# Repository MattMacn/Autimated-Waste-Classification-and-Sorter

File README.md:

# Automated Material Sorting System

## Overview

The **Automated Material Sorting System** is an embedded system designed to automatically identify and sort different types of waste.

The system uses an **ESP32 microcontroller** together with inductive, capacitive and ultrasonic sensors to identify materials and control a mechanical sorting mechanism using four servo motors.

The project combines **embedded software, electronics, PCB design and mechanical control** into a single automated system.

## Features

* Automatic material detection
* Metal detection using an inductive sensor
* Non-metal material detection using a capacitive sensor
* Ultrasonic sensing for object detection
* Automated mechanical sorting
* Four servo motors for material routing
* ESP32-based embedded control
* Custom PCB designed using KiCad
* Separate collection compartments for different materials

## System Architecture

```text

                            ^
                            |
          +-----------------+-----------------+
          |                 |                 |
          v                 v                 v
   +-------------+   +-------------+   +-------------+
   |  Inductive  |   | Capacitive  |   |  Ultrasonic |
   |   Sensor    |   |   Sensor    |   |   Sensor    |
   +-------------+   +-------------+   +-------------+
          +-----------------+-----------------+
                            |                 
                            |                                       
                            |
                            v
                  +-------------------+
                  |       ESP32       |
                  |                   |
                  |  Embedded Control |
                  +---------+---------+
                            |
                            v
                   +----------------+
                   | Material       |
                   | Classification |
                   +-------+--------+
                           |
                           v
                  +-------------------+
                  | Servo Actuators   |
                  |                   |
                  |   4 x SG90        |
                  +---------+---------+

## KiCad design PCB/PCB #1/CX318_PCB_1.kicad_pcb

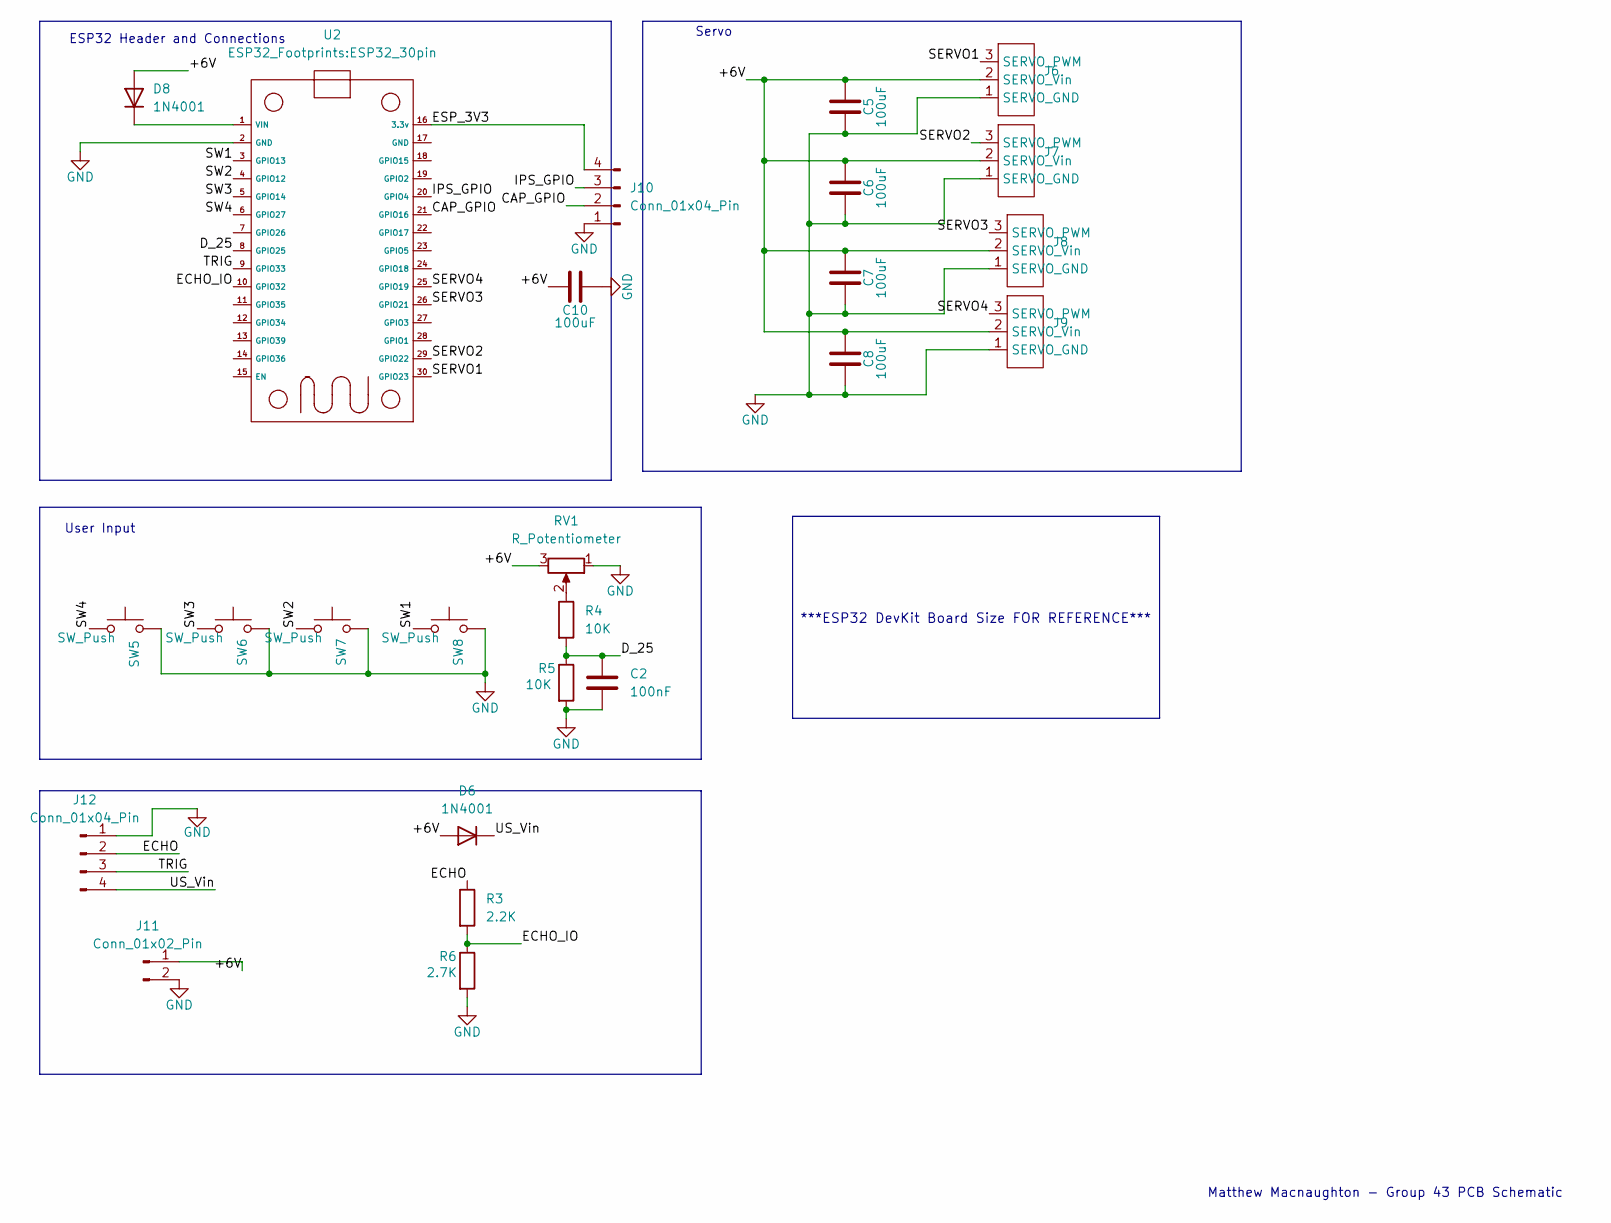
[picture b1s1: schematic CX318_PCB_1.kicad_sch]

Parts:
C2: 100nF; C_Disc_D5.0mm_W2.5mm_P5.00mm
C5, C6, C7, C8, C10: 100uF; C_Disc_D5.0mm_W2.5mm_P5.00mm
D6, D8: 1N4001; D_DO-41_SOD81_P10.16mm_Horizontal
J6, J7, J8, J9: PinHeader_1x03_P2.54mm_Vertical
J10: Conn_01x04_Pin; JST_XH_B4B-XH-A_1x04_P2.50mm_Vertical
J11: Conn_01x02_Pin; PinSocket_1x02_P2.54mm_Vertical
J12: Conn_01x04_Pin; PinSocket_1x04_P2.54mm_Vertical
R3: 2.2K; R_Axial_DIN0207_L6.3mm_D2.5mm_P7.62mm_Horizontal
R4, R5: 10K; R_Axial_DIN0207_L6.3mm_D2.5mm_P7.62mm_Horizontal
R6: 2.7K; R_Axial_DIN0207_L6.3mm_D2.5mm_P7.62mm_Horizontal
RV1: R_Potentiometer; Potentiometer_Bourns_3386P_Vertical
SW5, SW6, SW7, SW8: SW_Push; SW_PUSH_6mm
U2: ESP32_30pin

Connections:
/+6V: C5.1, C6.1, C7.1, C8.1, C10.2, D6.2 (A), D8.2 (A), J6.2 (SERVO_Vin), J7.2 (SERVO_Vin), J8.2 (SERVO_Vin), J9.2 (SERVO_Vin), J11.1, RV1.3
/CAP_GPIO: J10.2, U2.21 (GPIO16)
/D_25: C2.1, R4.2, R5.1, U2.8 (GPIO25)
/ECHO: J12.2, R3.1
/ECHO_IO: R3.2, R6.1, U2.10 (GPIO32)
/ESP_3V3: J10.4, U2.16 (3.3v)
/IPS_GPIO: J10.3, U2.20 (GPIO4)
/SERVO1: J6.3 (SERVO_PWM), U2.30 (GPIO23)
/SERVO2: J7.3 (SERVO_PWM), U2.29 (GPIO22)
/SERVO3: J8.3 (SERVO_PWM), U2.26 (GPIO21)
/SERVO4: J9.3 (SERVO_PWM), U2.25 (GPIO19)
/SW1: SW8.1, U2.3 (GPIO13)
/SW2: SW7.1, U2.4 (GPIO12)
/SW3: SW6.1, U2.5 (GPIO14)
/SW4: SW5.1, U2.6 (GPIO27)
/TRIG: J12.3, U2.9 (GPIO33)
/US_Vin: D6.1 (K), J12.4
GND: C2.2, C5.2, C6.2, C7.2, C8.2, C10.1, J6.1 (SERVO_GND), J7.1 (SERVO_GND), J8.1 (SERVO_GND), J9.1 (SERVO_GND), J10.1, J11.2, J12.1, R5.2, R6.2, RV1.1, SW5.2, SW6.2, SW7.2, SW8.2, U2.2 (GND)
unnamed: D8.1 (K), U2.1 (VIN)
unnamed: R4.1, RV1.2

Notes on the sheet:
User Input
Matthew Macnaughton - Group 43 PCB Schematic
Servo
ESP32 Header and Connections
***ESP32 DevKit Board Size FOR REFERENCE***

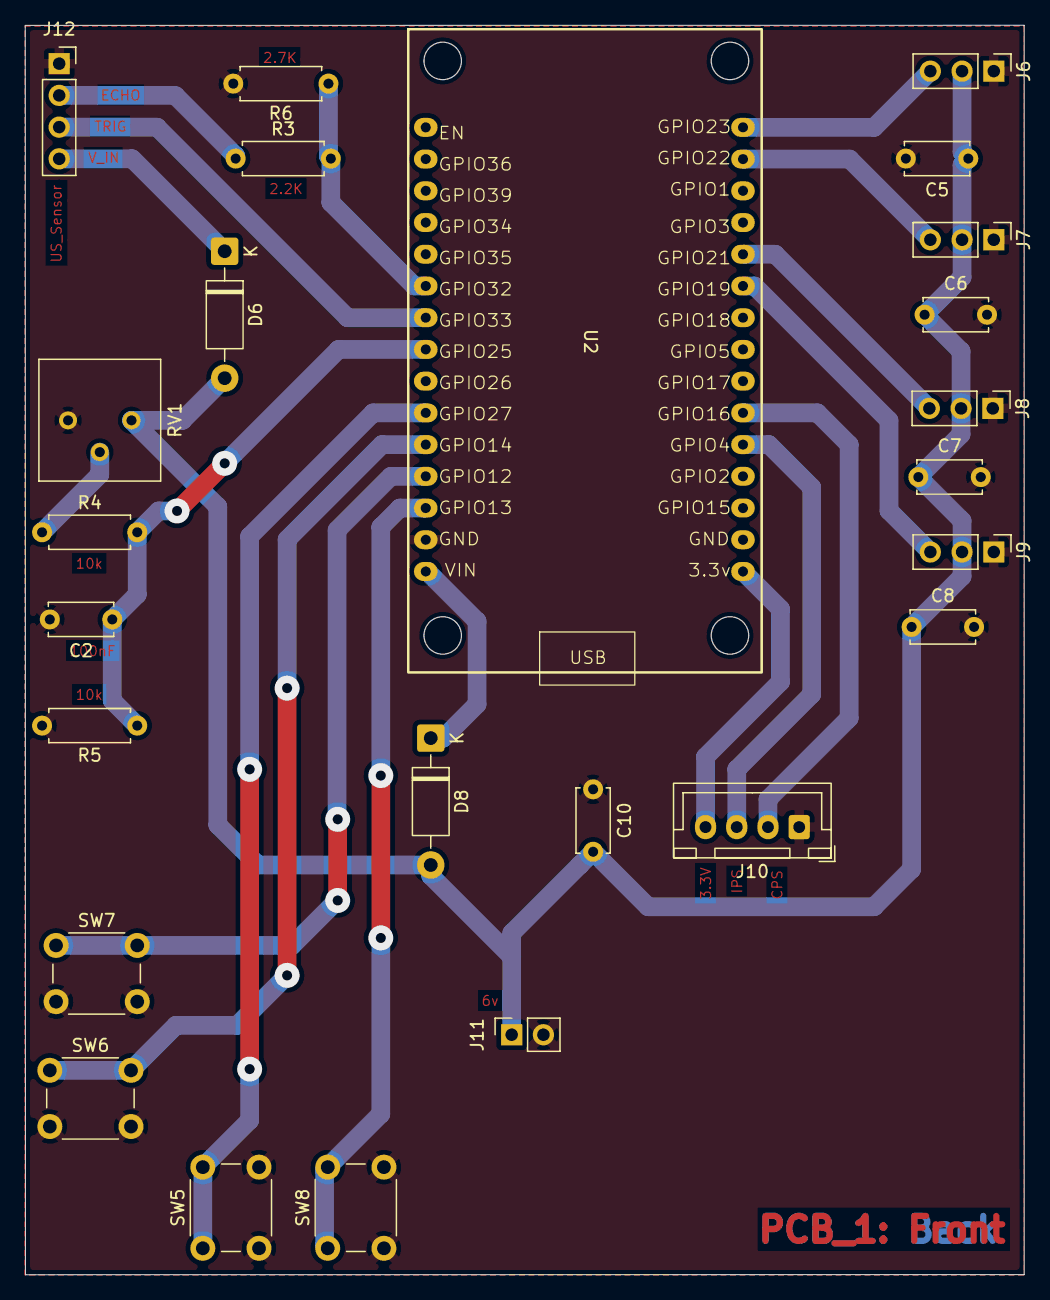
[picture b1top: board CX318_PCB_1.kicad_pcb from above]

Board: 2 copper layers, 80.0 x 100.0 mm, 25 parts (0 on the bottom side), 20 nets.

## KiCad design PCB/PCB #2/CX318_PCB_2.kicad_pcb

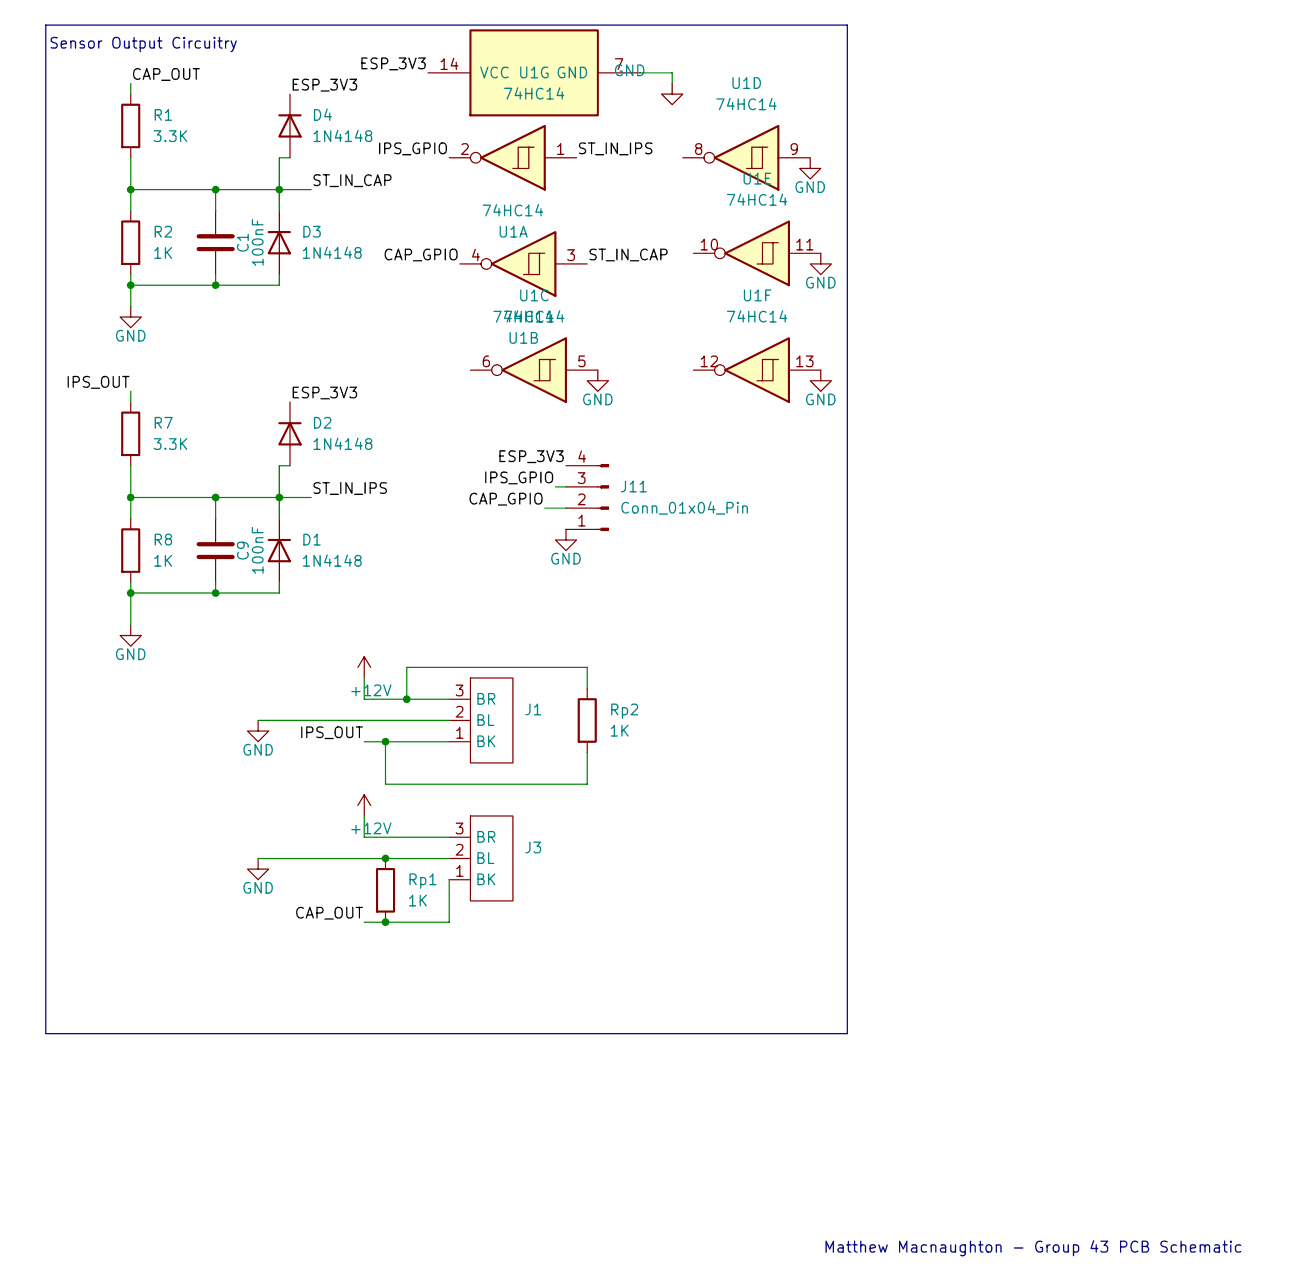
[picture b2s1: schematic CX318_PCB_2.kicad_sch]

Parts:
C1, C9: 100nF; C_Disc_D5.0mm_W2.5mm_P5.00mm
D1, D2, D3, D4: 1N4148; D_DO-35_SOD27_P7.62mm_Horizontal
J1, J3: PinHeader_1x03_P2.54mm_Vertical
J11: Conn_01x04_Pin; JST_XH_B4B-XH-A_1x04_P2.50mm_Vertical
R1, R7: 3.3K; R_Axial_DIN0207_L6.3mm_D2.5mm_P7.62mm_Horizontal
R2, R8: 1K; R_Axial_DIN0207_L6.3mm_D2.5mm_P7.62mm_Horizontal
Rp1, Rp2: 1K; R_Axial_DIN0207_L6.3mm_D2.5mm_P7.62mm_Horizontal
U1: 74HC14; DIP-14_W7.62mm

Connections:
+12V: J1.3 (BR), J3.3 (BR), Rp2.1; also elsewhere on the board
/CAP_GPIO: J11.2, U1.4
/CAP_OUT: J3.1 (BK), R1.1, Rp1.2
/ESP_3V3: D2.1 (K), D4.1 (K), J11.4, U1.14 (VCC)
/IPS_GPIO: J11.3, U1.2
/IPS_OUT: J1.1 (BK), R7.1, Rp2.2
/ST_IN_CAP: C1.1, D3.1 (K), D4.2 (A), R1.2, R2.1, U1.3
/ST_IN_IPS: C9.1, D1.1 (K), D2.2 (A), R7.2, R8.1, U1.1
GND: C1.2, C9.2, D1.2 (A), D3.2 (A), J1.2 (BL), J3.2 (BL), J11.1, R2.2, R8.2, Rp1.1, U1.5, U1.7 (GND), U1.9, U1.11, U1.13; also elsewhere on the board

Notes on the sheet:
Matthew Macnaughton - Group 43 PCB Schematic
Sensor Output Circuitry

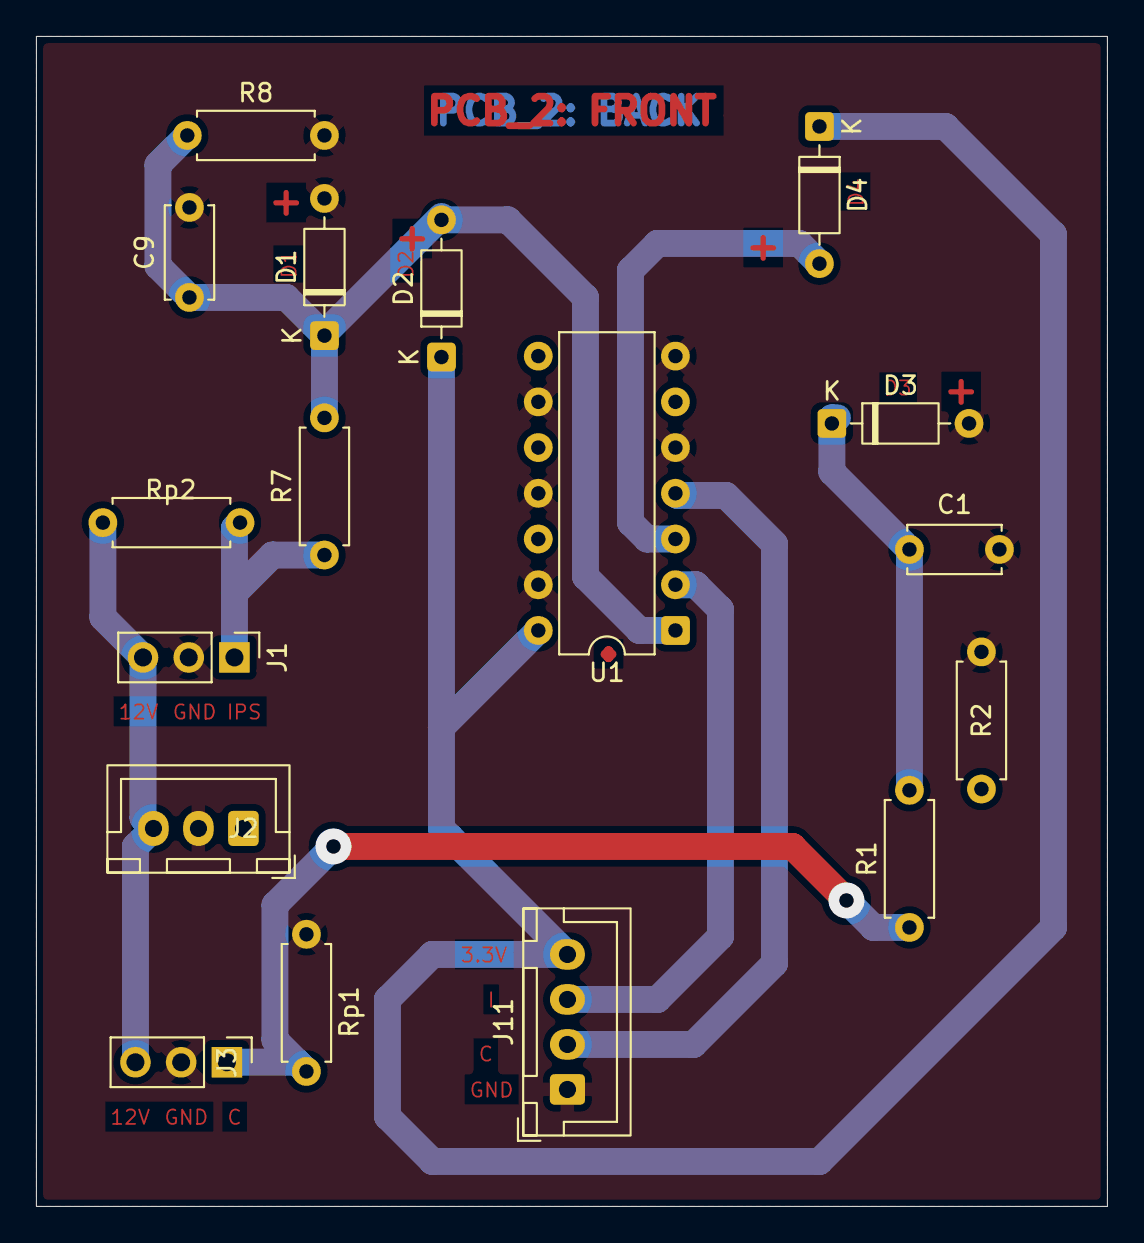
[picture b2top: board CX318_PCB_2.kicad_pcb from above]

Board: 2 copper layers, 59.5 x 65.0 mm, 17 parts (0 on the bottom side), 9 nets.

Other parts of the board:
J2: Conn_01x03_Pin; JST_XH_B3B-XH-A_1x03_P2.50mm_Vertical

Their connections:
+12V: J2.3; also elsewhere on the board
GND: J2.2; also elsewhere on the board
